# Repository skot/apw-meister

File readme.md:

# apw-meister

A CH32X035F8U6-based USB interface for the Antminer APW12 PSU data connector, derived from AditBoard v2.

The `master` branch contains the CH32 hardware migration. The RP2354A version, including its initial routing, is preserved on `main` at `2b5b7f9`.

The CH32 provides internal flash, clock and core regulation. The board retains its USB-powered 3.3 V LDO and adds MOSFET isolation to prevent APW I2C pull-ups from backfeeding an unpowered MCU. See the [schematic notes and firmware pin map](doc/apw-meister-schematic.md) and [BOM](doc/apw-meister-bom.csv).

The PCB is 14 × 28 mm, reduced from 16 × 35 mm (30% less area), with six copper layers, APW12 at the top edge and USB at the bottom. Placement groups the APW interface below its connector, the CH32 in the middle, and USB protection beside the USB connector. All normally fitted SMD parts are on top. BOOT and RESET remain optional bottom-side DNP development buttons. All purchased parts have JLCPCB/LCSC numbers and project-local 3D models; the MCU model is a generic QFN visualization.

The first CH32 routing pass is complete, including ground and power planes. In1.Cu and In4.Cu provide ground references; In2.Cu distributes 3.3 V and In3.Cu distributes 5 V, with a few signal crossings on the power layers. Final USB geometry and fabrication review, the inherited USB connector hole-clearance issues, and the CH32 firmware port remain. Existing AditBoard artwork, mechanical and manufacturing outputs are historical and must not be used to order this revision.

Validation: the unchanged schematic has zero ERC violations; all 118 pad-to-net assignments match. Filled-board DRC has zero unrouted connections, zero schematic-parity issues, two inherited USB hole-clearance errors, and two warnings: a leftover BOOT trace stub and the decorative logo’s missing courtyard. See the [validation record](doc/ch32-validation.json).

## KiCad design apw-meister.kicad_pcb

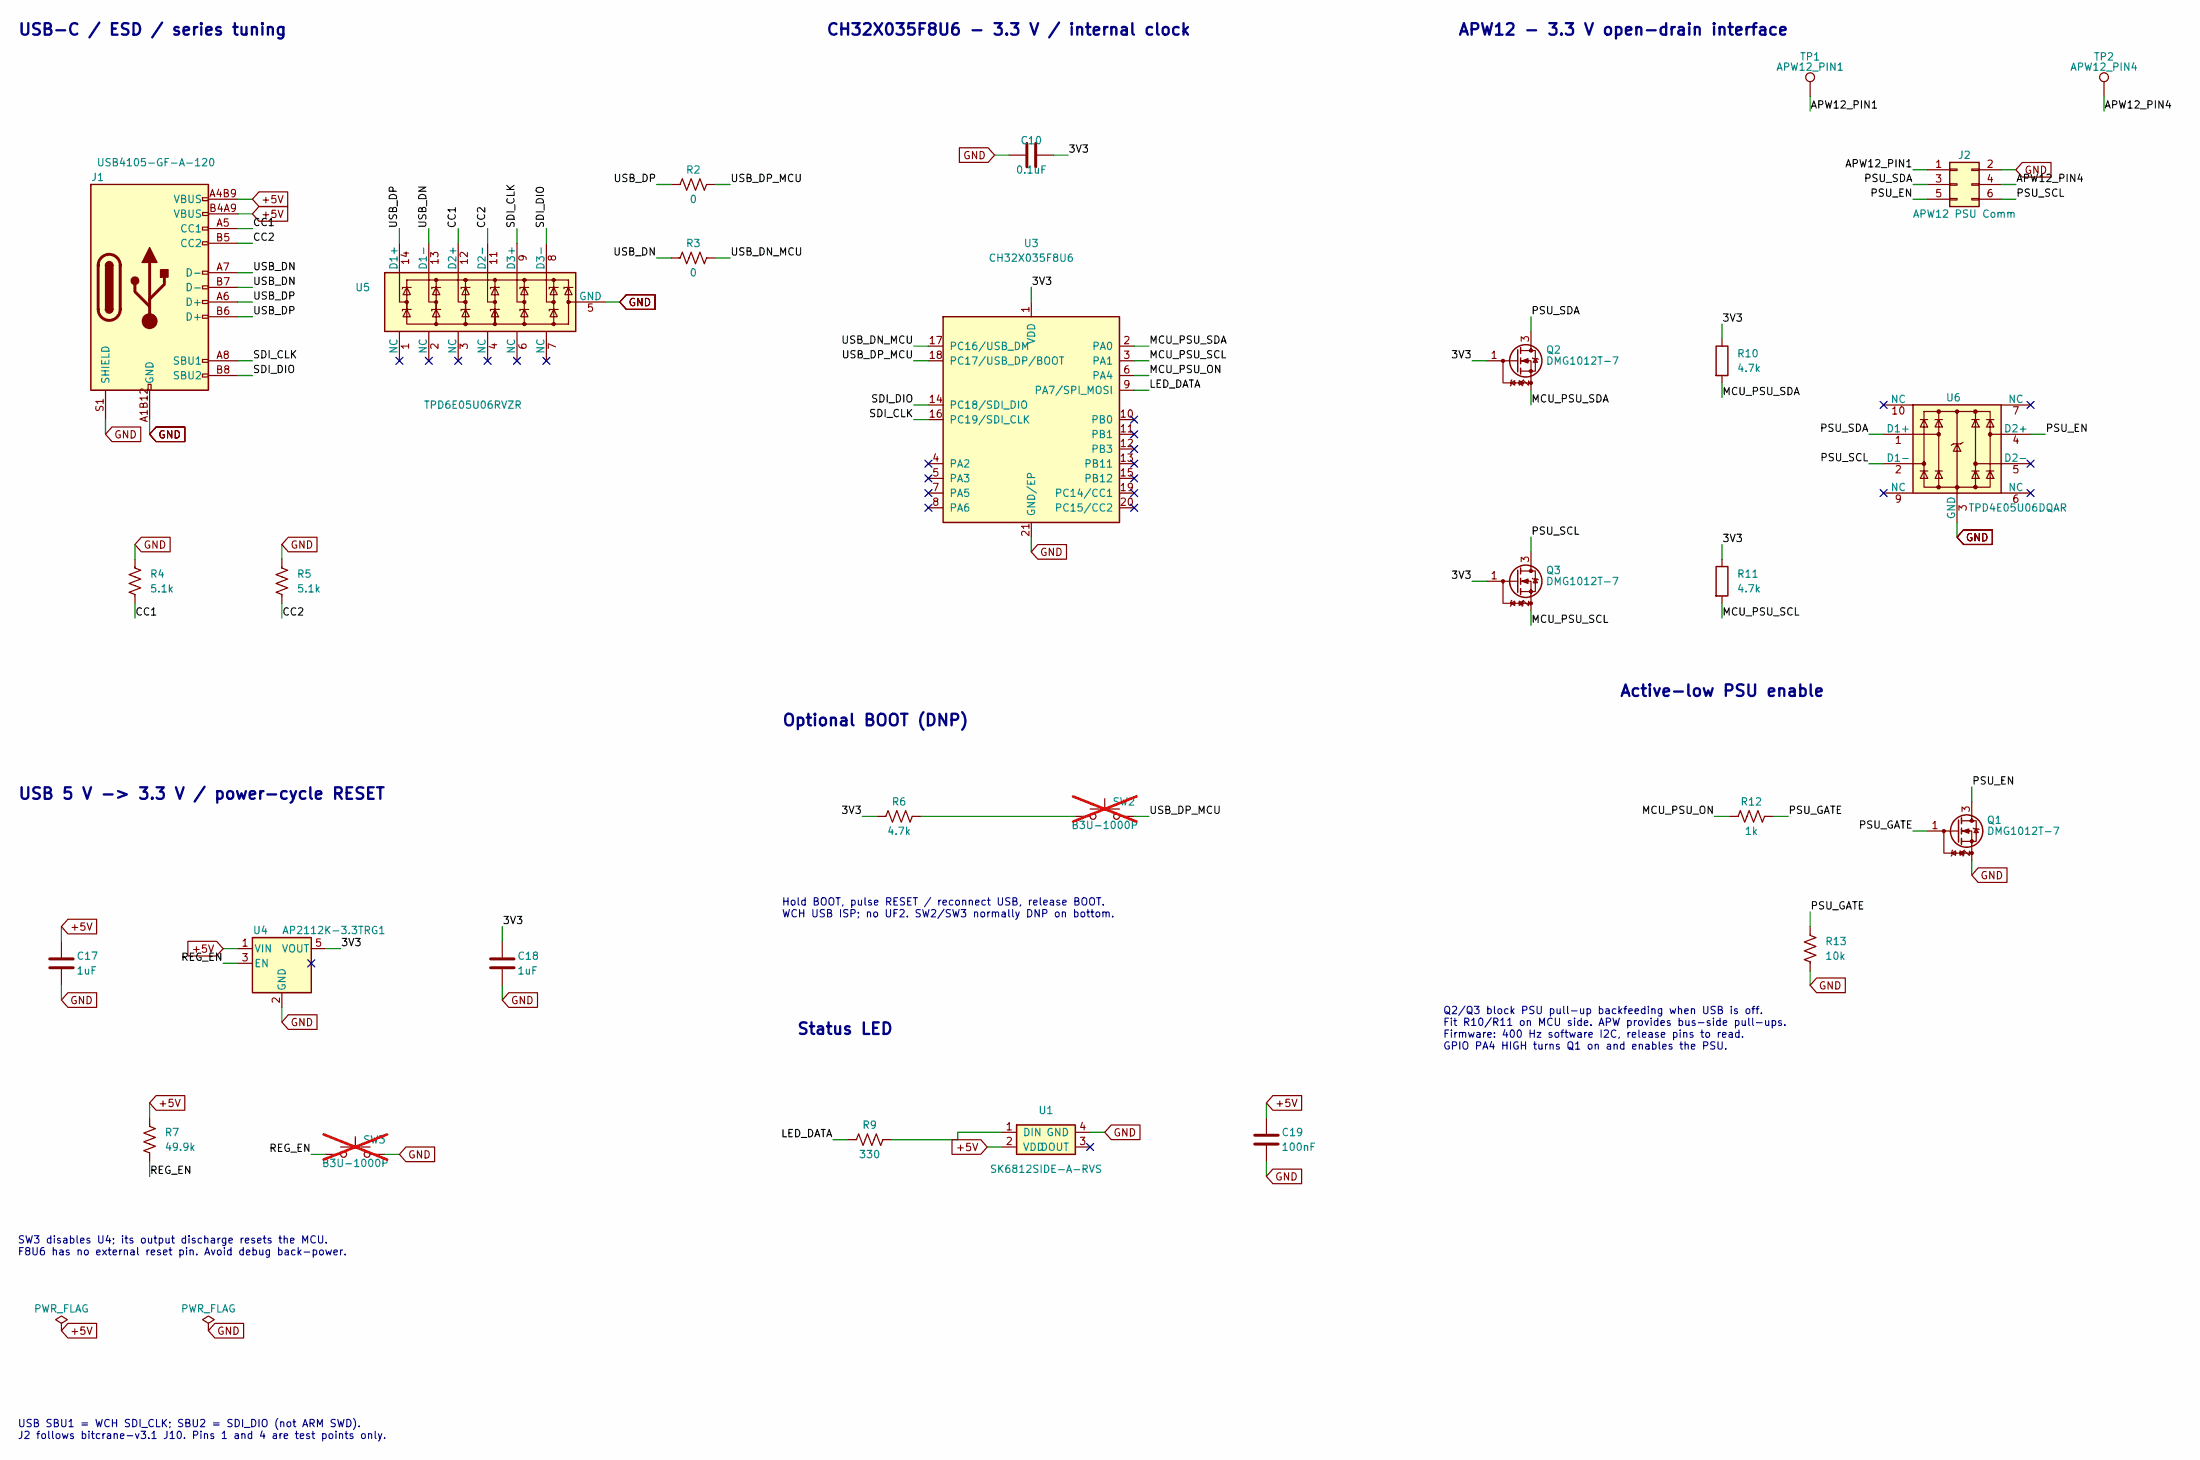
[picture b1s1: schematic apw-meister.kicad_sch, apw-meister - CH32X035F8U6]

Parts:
C10: 0.1uF; C_0402_1005Metric; Tolerance ±10%; Voltage 50V; MPN CL05B104KB54PNC; JLC Part Basic Part
C17, C18: 1uF; C_0402_1005Metric; Tolerance ±10%; Voltage 25V; MPN CL05A105KA5NQNC; JLC Part Basic Part
C19: 100nF; C_0402_1005Metric; Tolerance ±10%; Voltage 50V; MPN CL05B104KB54PNC; JLC Part Basic Part
J1: USB4105-GF-A-120; USB_C_Receptacle_GCT_USB4105-xx-A_16P_TopMnt_Horizontal; Voltage 48V; MPN USB4105-GF-A-120; JLC Part Extended Part
J2: APW12 PSU Comm; CONN-TH_6P-P2.00_PHD-2X3A; Voltage 250V; MPN HC-PHD-2*3A; JLC Part Extended Part
Q1, Q2, Q3: DMG1012T-7; SOT-523; MPN DMG1012T-7; JLC Part Extended Part
R2, R3: 0; R_0402_1005Metric; Tolerance ±1%; MPN 0402WGF0000TCE; JLC Part Basic Part
R4, R5: 5.1k; R_0402_1005Metric; Tolerance ±1%; MPN 0402WGF5101TCE; JLC Part Basic Part
R6, R10, R11: 4.7k; R_0402_1005Metric; Tolerance ±1%; MPN 0402WGF4701TCE; JLC Part Basic Part
R7: 49.9k; R_0402_1005Metric; Tolerance ±1%; MPN RC0402FR-0749K9L; JLC Part Extended Part
R9: 330; R_0402_1005Metric; Tolerance ±1%; MPN 0402WGF3300TCE; JLC Part Basic Part
R12: 1k; R_0402_1005Metric; Tolerance ±1%; MPN RC0402FR-071KL; JLC Part Extended Part
R13: 10k; R_0402_1005Metric; Tolerance ±1%; MPN 0402WGF1002TCE; JLC Part Basic Part
SW2, SW3: B3U-1000P; SW_SPST_B3U-1000P; Voltage 12V; MPN B3U-1000P; JLC Part Extended Part; not fitted
TP1: APW12_PIN1; TestPoint_Pad_D1.0mm
TP2: APW12_PIN4; TestPoint_Pad_D1.0mm
U1: SK6812SIDE-A-RVS; LED-SMD_4P-L4.0-W1.6-L; MPN SK6812SIDE-A-RVS; JLC Part Extended Part
U3: CH32X035F8U6; VQFN-20-1EP_3x3mm_P0.4mm_EP1.7x1.7mm; MPN CH32X035F8U6; JLC Part Extended Part
U4: AP2112K-3.3TRG1; SOT-25-5_L2.9-W1.6-P0.95-LS2.8-BL; MPN AP2112K-3.3TRG1; JLC Part Extended Part
U5: TPD6E05U06RVZR; Texas_R-PUSON-N14; MPN TPD6E05U06RVZR; JLC Part Extended Part
U6: TPD4E05U06DQAR; USON-10_2.5x1.0mm_P0.5mm; MPN TPD4E05U06DQAR; JLC Part Extended Part

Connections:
/3V3: C10.2, C18.1, Q2.1 (G), Q3.1 (G), R6.1, R10.1, R11.1, U3.1 (VDD), U4.5 (VOUT)
/APW12_PIN1: J2.1, TP1.1 (1_1)
/APW12_PIN4: J2.4, TP2.1 (1_1)
/CC1: J1.A5 (CC1), R4.2, U5.12 (D2+)
/CC2: J1.B5 (CC2), R5.2, U5.11 (D2-)
/LED_DATA: R9.1, U3.9 (PA7/SPI_MOSI)
/MCU_PSU_ON: R12.1, U3.6 (PA4)
/MCU_PSU_SCL: Q3.2 (S), R11.2, U3.3 (PA1)
/MCU_PSU_SDA: Q2.2 (S), R10.2, U3.2 (PA0)
/PSU_EN: J2.5, Q1.3 (D), U6.4 (D2+)
/PSU_GATE: Q1.1 (G), R12.2, R13.1
/PSU_SCL: J2.6, Q3.3 (D), U6.2 (D1-)
/PSU_SDA: J2.3, Q2.3 (D), U6.1 (D1+)
/REG_EN: R7.2, SW3.1, U4.3 (EN)
/SDI_CLK: J1.A8 (SBU1), U3.16 (PC19/SDI_CLK), U5.9 (D3+)
/SDI_DIO: J1.B8 (SBU2), U3.14 (PC18/SDI_DIO), U5.8 (D3-)
/USB_DN: J1.A7 (D-), J1.B7 (D-), R3.1, U5.13 (D1-)
/USB_DN_MCU: R3.2, U3.17 (PC16/USB_DM)
/USB_DP: J1.A6 (D+), J1.B6 (D+), R2.1, U5.14 (D1+)
/USB_DP_MCU: R2.2, SW2.2, U3.18 (PC17/USB_DP/BOOT)
unnamed: R6.2, SW2.1
unnamed: R9.2, U1.1 (DIN)

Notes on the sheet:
Hold BOOT, pulse RESET / reconnect USB, release BOOT. WCH USB ISP; no UF2. SW2/SW3 normally DNP on bottom.
SW3 disables U4; its output discharge resets the MCU. F8U6 has no external reset pin. Avoid debug back-power.
Q2/Q3 block PSU pull-up backfeeding when USB is off. Fit R10/R11 on MCU side. APW provides bus-side pull-ups. Firmware: 400 Hz software I2C, release pins to read. GPIO PA4 HIGH turns Q1 on and enables the PSU.
APW12 - 3.3 V open-drain interface
Status LED
USB 5 V -> 3.3 V / power-cycle RESET
USB SBU1 = WCH SDI_CLK; SBU2 = SDI_DIO (not ARM SWD). J2 follows bitcrane-v3.1 J10. Pins 1 and 4 are test points only.
CH32X035F8U6 - 3.3 V / internal clock
Optional BOOT (DNP)
Active-low PSU enable
USB-C / ESD / series tuning

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
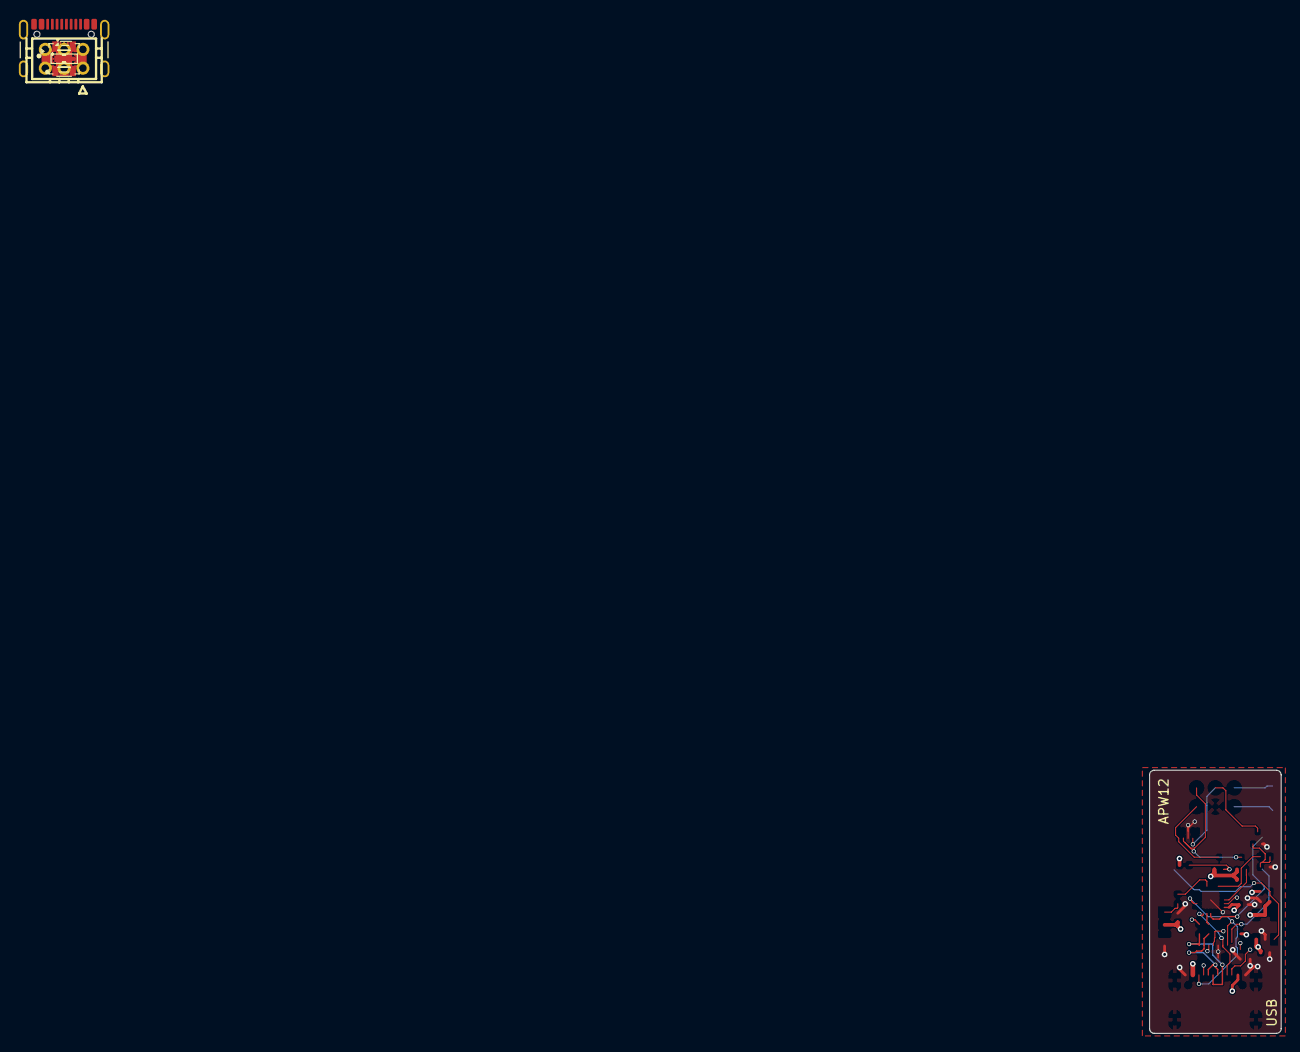
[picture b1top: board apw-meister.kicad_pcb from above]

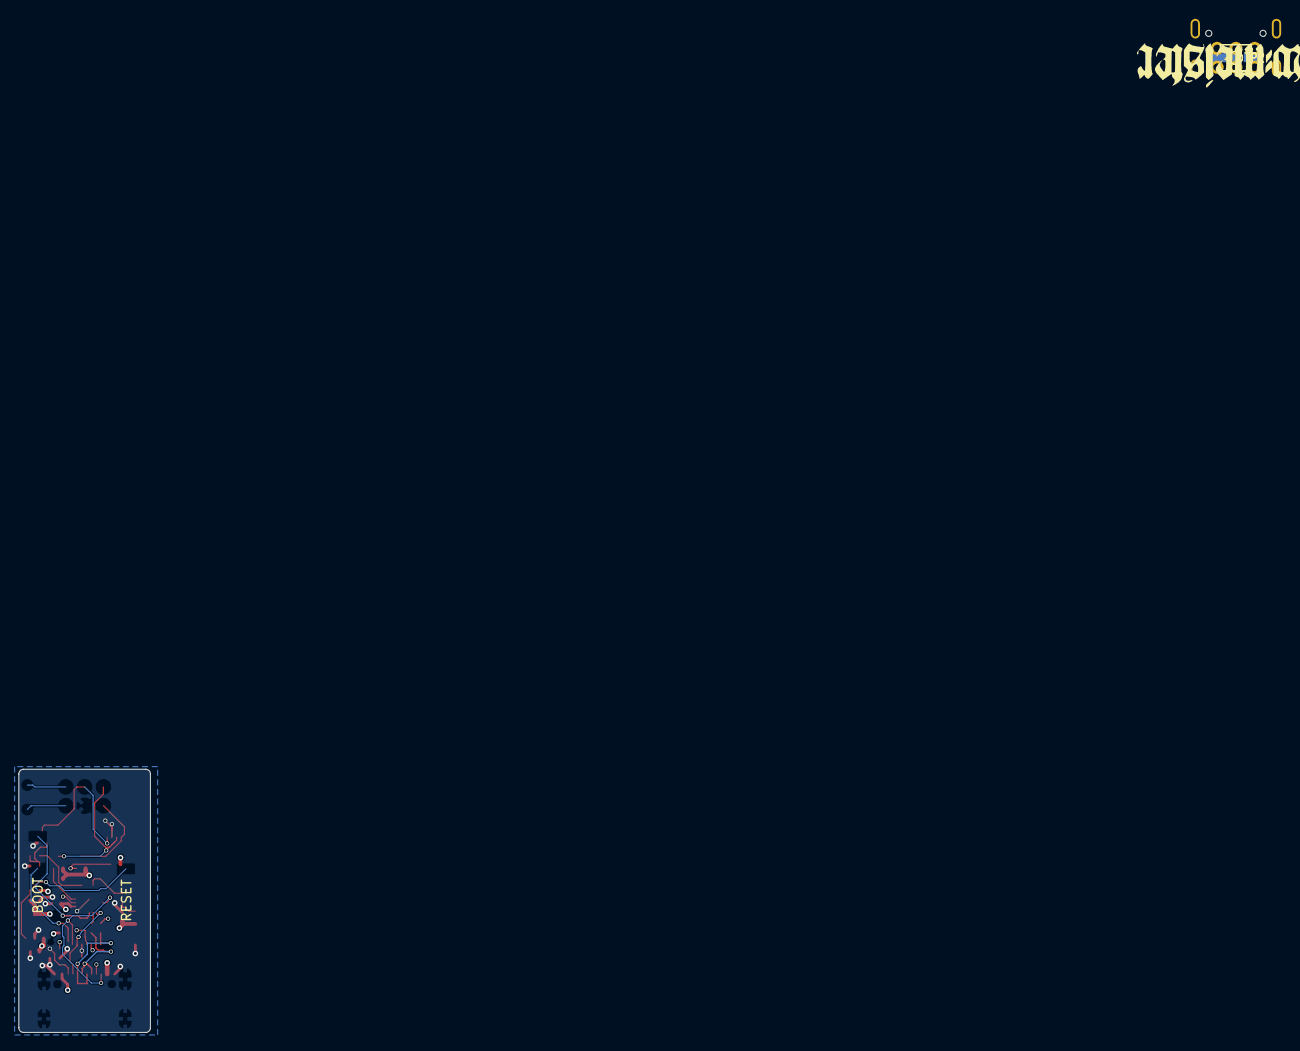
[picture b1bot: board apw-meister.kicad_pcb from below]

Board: 6 copper layers, 14.0 x 28.0 mm, 29 parts (4 on the bottom side), 24 nets.

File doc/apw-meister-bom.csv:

Reference,Value,Footprint,Manufacturer,MPN,JLCPCB Part #,DNP,Assembly note
C10,0.1uF,aditBoard:C_0402_1005Metric,Samsung Electro-Mechanics,CL05B104KB54PNC,C307331,,
C17,1uF,aditBoard:C_0402_1005Metric,Samsung Electro-Mechanics,CL05A105KA5NQNC,C52923,,
C18,1uF,aditBoard:C_0402_1005Metric,Samsung Electro-Mechanics,CL05A105KA5NQNC,C52923,,
C19,100nF,aditBoard:C_0402_1005Metric,Samsung Electro-Mechanics,CL05B104KB54PNC,C307331,,
J1,USB4105-GF-A-120,aditBoard:USB_C_Receptacle_GCT_USB4105-xx-A_16P_TopMnt_Horizontal,Global Connector Technology,USB4105-GF-A-120,C5184243,,
J2,APW12 PSU Comm,aditBoard:CONN-TH_6P-P2.00_PHD-2X3A,HCTL,HC-PHD-2*3A,C2845614,,
Q1,DMG1012T-7,aditBoard:SOT-523,Diodes Incorporated,DMG1012T-7,C20512,,
Q2,DMG1012T-7,aditBoard:SOT-523,Diodes Incorporated,DMG1012T-7,C20512,,
Q3,DMG1012T-7,aditBoard:SOT-523,Diodes Incorporated,DMG1012T-7,C20512,,
R2,0,aditBoard:R_0402_1005Metric,UNI-ROYAL(Uniroyal Elec),0402WGF0000TCE,C17168,,USB series tuning position; fit 0 ohm for WCH reference circuit.
R3,0,aditBoard:R_0402_1005Metric,UNI-ROYAL(Uniroyal Elec),0402WGF0000TCE,C17168,,USB series tuning position; fit 0 ohm for WCH reference circuit.
R4,5.1k,aditBoard:R_0402_1005Metric,UNI-ROYAL(Uniroyal Elec),0402WGF5101TCE,C25905,,
R5,5.1k,aditBoard:R_0402_1005Metric,UNI-ROYAL(Uniroyal Elec),0402WGF5101TCE,C25905,,
R6,4.7k,aditBoard:R_0402_1005Metric,UNI-ROYAL(Uniroyal Elec),0402WGF4701TCE,C25900,,BOOT pull-up to 3.3 V through optional SW2.
R7,49.9k,aditBoard:R_0402_1005Metric,YAGEO,RC0402FR-0749K9L,C137969,,
R9,330,aditBoard:R_0402_1005Metric,UNI-ROYAL(Uniroyal Elec),0402WGF3300TCE,C25104,,
R10,4.7k,aditBoard:R_0402_1005Metric,UNI-ROYAL(Uniroyal Elec),0402WGF4701TCE,C25900,,FIT: MCU-side 4.7k pull-up; APW side uses PSU pull-ups.
R11,4.7k,aditBoard:R_0402_1005Metric,UNI-ROYAL(Uniroyal Elec),0402WGF4701TCE,C25900,,FIT: MCU-side 4.7k pull-up; APW side uses PSU pull-ups.
R12,1k,aditBoard:R_0402_1005Metric,YAGEO,RC0402FR-071KL,C106235,,
R13,10k,aditBoard:R_0402_1005Metric,UNI-ROYAL(Uniroyal Elec),0402WGF1002TCE,C25744,,
SW2,B3U-1000P,aditBoard:SW_SPST_B3U-1000P,Omron Electronics,B3U-1000P,C231329,DNP,DNP: optional bottom-side development button.
SW3,B3U-1000P,aditBoard:SW_SPST_B3U-1000P,Omron Electronics,B3U-1000P,C231329,DNP,DNP: optional bottom-side development button.
TP1,APW12_PIN1,aditBoard:TestPoint_Pad_D1.0mm,,,,,Bare PCB copper test pad; no purchased component or JLCPCB part number.
TP2,APW12_PIN4,aditBoard:TestPoint_Pad_D1.0mm,,,,,Bare PCB copper test pad; no purchased component or JLCPCB part number.
U1,SK6812SIDE-A-RVS,aditBoard:LED-SMD_4P-L4.0-W1.6-L,OPSCO Optoelectronics,SK6812SIDE-A-RVS,C2890037,,
U3,CH32X035F8U6,aditBoard:VQFN-20-1EP_3x3mm_P0.4mm_EP1.7x1.7mm,WCH (Jiangsu Qin Heng),CH32X035F8U6,C42442062,,QFN20 3x3 mm; exposed ground pad is pad 21 in this library.
U4,AP2112K-3.3TRG1,aditBoard:SOT-25-5_L2.9-W1.6-P0.95-LS2.8-BL,Diodes Incorporated,AP2112K-3.3TRG1,C51118,,
U5,TPD6E05U06RVZR,aditBoard:Texas_R-PUSON-N14,Texas Instruments,TPD6E05U06RVZR,C962978,,
U6,TPD4E05U06DQAR,aditBoard:USON-10_2.5x1.0mm_P0.5mm,Texas Instruments,TPD4E05U06DQAR,C138714,,
